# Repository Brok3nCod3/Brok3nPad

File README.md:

# Brok3nPad
My hackpad (it's really bad)

I spent no less than 12 hours on this, and due to family related issues (divorced parents) I'm unable to finish the QMK firmware, and can't access KiCad for a week after writing this.
I don't know how to add folders, I don't use Github that much.
I added everything I thought might be useful, and I don't have time to add a BOM or learn how to
Honestly, I'm just glad that people who saw what I was doing as they walked by thought I was smart because they didn't understand what I was doing (neither did I)

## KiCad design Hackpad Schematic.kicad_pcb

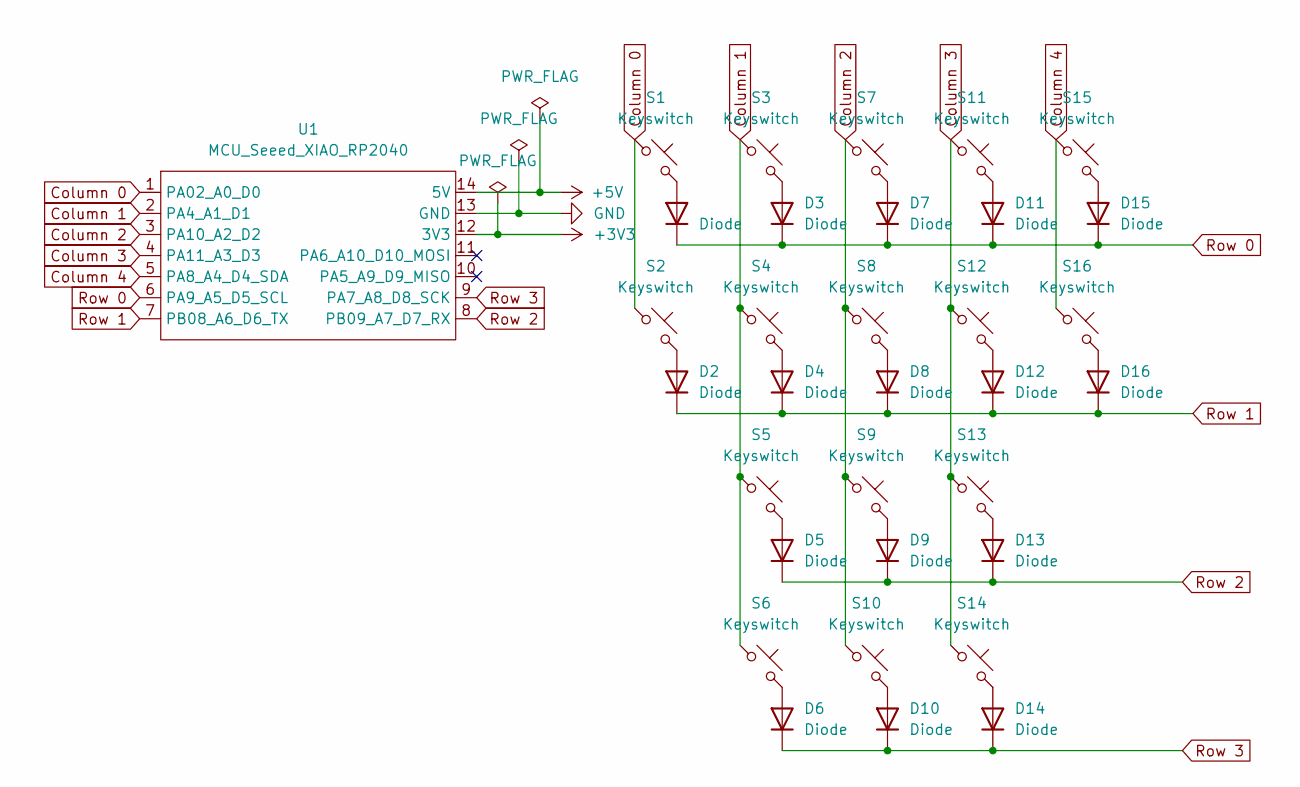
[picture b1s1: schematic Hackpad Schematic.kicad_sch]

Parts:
D1, D2, D3, D4, D5, D6, D7, D8, D9, D10, D11, D12, D13, D14, D15, D16: Diode; Diode_DO-35
S1, S2, S3, S4, S5, S6, S7, S8, S9, S10, S11, S12, S13, S14, S15, S16: Keyswitch; MX-Solderable-1U
U1: MCU_Seeed_XIAO_RP2040; Seeed_XIAO_RP2040

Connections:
+3V3: U1.12 (3V3)
+5V: U1.14 (5V)
Column 0: S1.1, S2.1, U1.1 (PA02_A0_D0)
Column 1: S3.1, S4.1, S5.1, S6.1, U1.2 (PA4_A1_D1)
Column 2: S7.1, S8.1, S9.1, S10.1, U1.3 (PA10_A2_D2)
Column 3: S11.1, S12.1, S13.1, S14.1, U1.4 (PA11_A3_D3)
Column 4: S15.1, S16.1, U1.5 (PA8_A4_D4_SDA)
GND: U1.13 (GND)
unnamed: D1.2 (A), S1.2
unnamed: D2.2 (A), S2.2
unnamed: D3.2 (A), S3.2
unnamed: D4.2 (A), S4.2
unnamed: D5.2 (A), S5.2
unnamed: D6.2 (A), S6.2
unnamed: D7.2 (A), S7.2
unnamed: D8.2 (A), S8.2
unnamed: D9.2 (A), S9.2
unnamed: D10.2 (A), S10.2
unnamed: D11.2 (A), S11.2
unnamed: D12.2 (A), S12.2
unnamed: D13.2 (A), S13.2
unnamed: D14.2 (A), S14.2
unnamed: D15.2 (A), S15.2
unnamed: D16.2 (A), S16.2
Row 0: D1.1 (K), D3.1 (K), D7.1 (K), D11.1 (K), D15.1 (K), U1.6 (PA9_A5_D5_SCL)
Row 1: D2.1 (K), D4.1 (K), D8.1 (K), D12.1 (K), D16.1 (K), U1.7 (PB08_A6_D6_TX)
Row 2: D5.1 (K), D9.1 (K), D13.1 (K), U1.8 (PB09_A7_D7_RX)
Row 3: D6.1 (K), D10.1 (K), D14.1 (K), U1.9 (PA7_A8_D8_SCK)

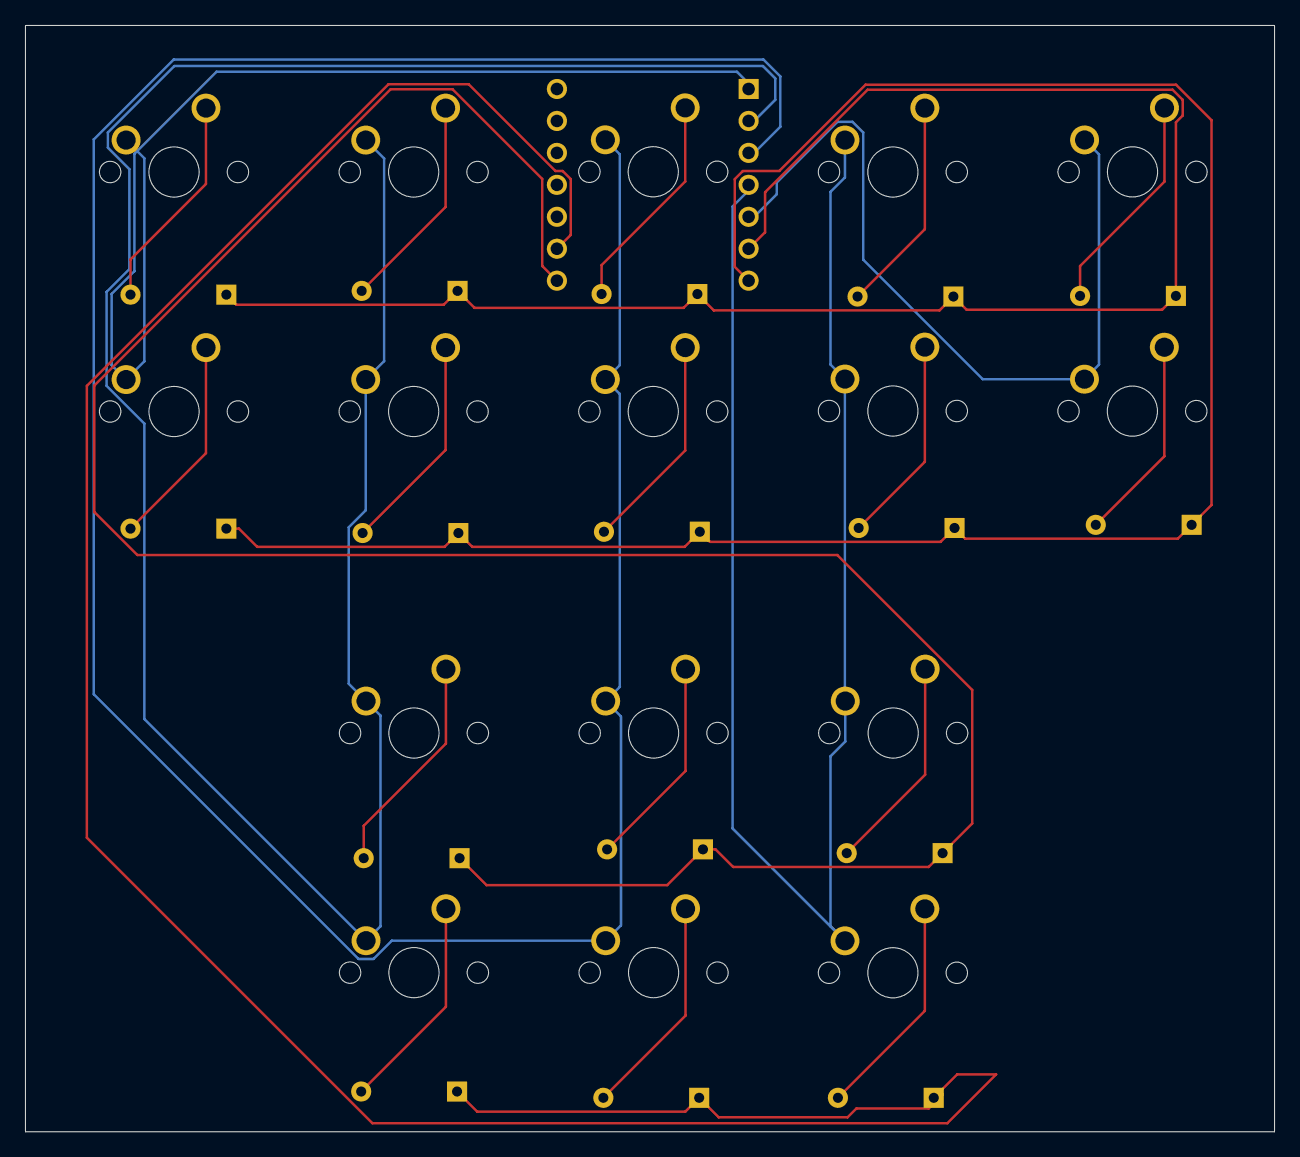
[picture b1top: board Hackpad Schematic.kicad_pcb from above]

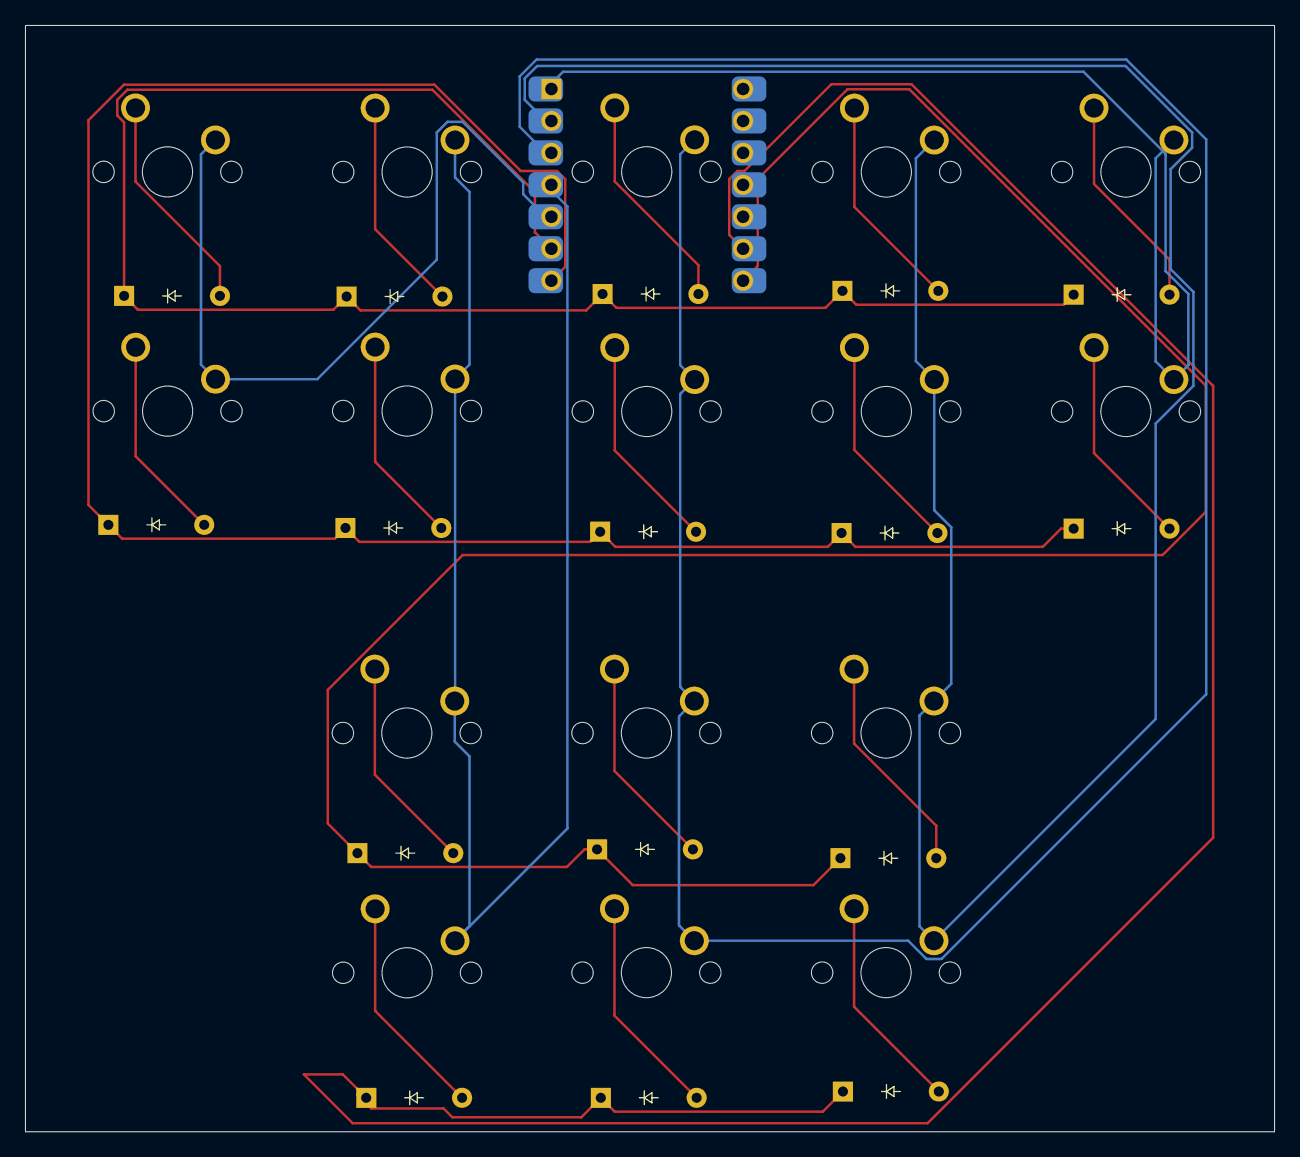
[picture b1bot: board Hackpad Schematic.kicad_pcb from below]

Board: 2 copper layers, 99.3 x 88.0 mm, 33 parts (17 on the bottom side), 25 nets.
